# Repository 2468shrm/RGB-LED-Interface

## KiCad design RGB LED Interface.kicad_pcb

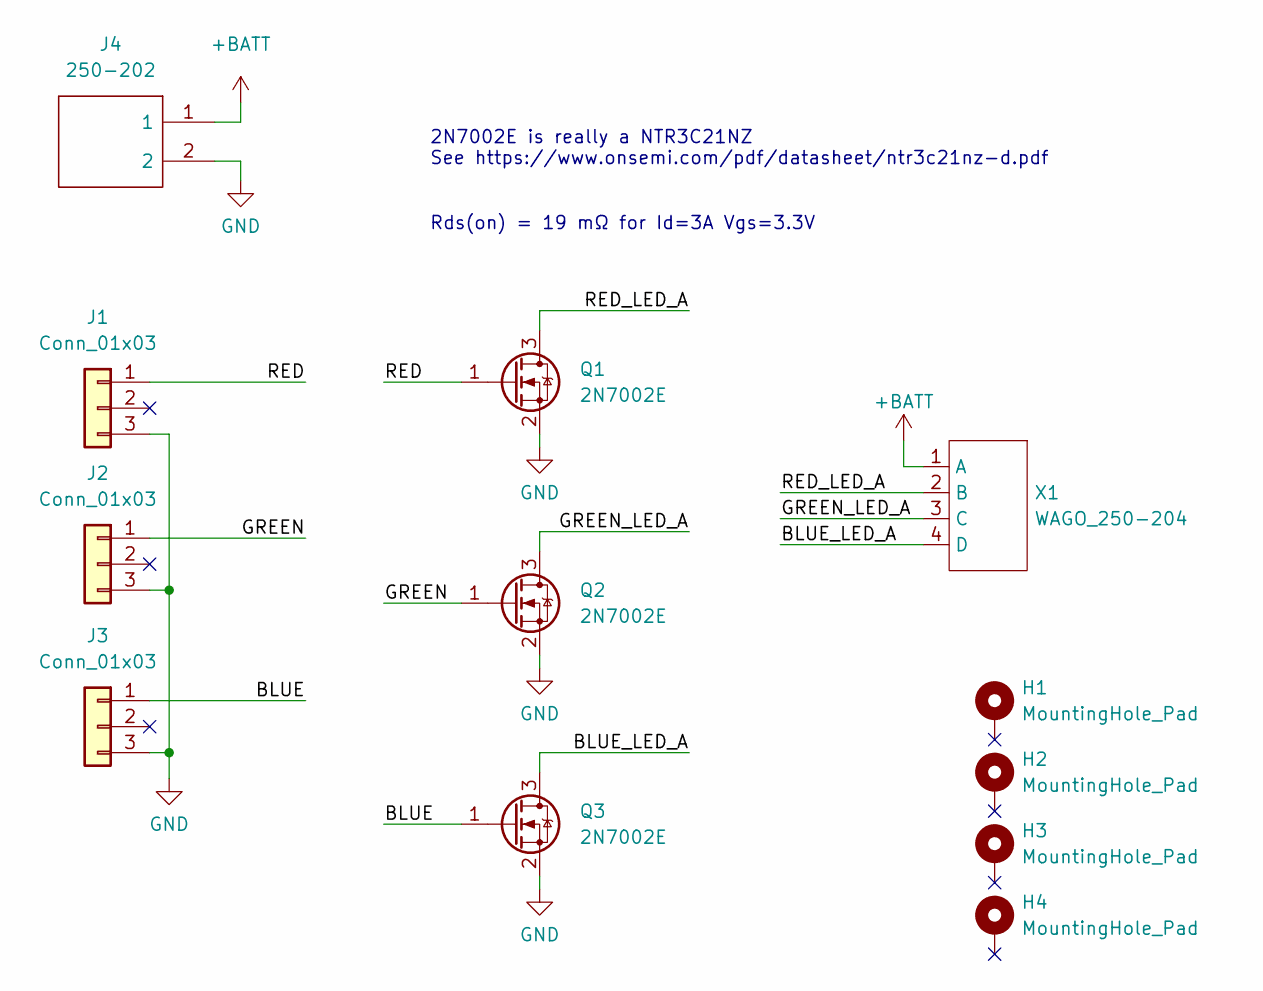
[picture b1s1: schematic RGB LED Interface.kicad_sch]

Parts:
H1: MountingHole_Pad
H2, H3, H4: MountingHole_Pad; MountingHole_2.2mm_M2_ISO7380_Pad
J1, J2, J3: Conn_01x03; PinHeader_1x03_P2.54mm_Vertical
J4: 250-202; 250202; Manufacturer_Part_Number 250-202
Q1, Q2, Q3: 2N7002E; SOT-23
X1: WAGO_250-204; WAGO 250-204

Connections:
+BATT: J4.1, X1.1 (A)
/BLUE: J3.1, Q3.1 (G)
/BLUE_LED_A: Q3.3 (D), X1.4 (D)
/GREEN: J2.1, Q2.1 (G)
/GREEN_LED_A: Q2.3 (D), X1.3 (C)
/RED: J1.1, Q1.1 (G)
/RED_LED_A: Q1.3 (D), X1.2 (B)
GND: J1.3, J2.3, J3.3, J4.2, Q1.2 (S), Q2.2 (S), Q3.2 (S)

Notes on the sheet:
2N7002E is really a NTR3C21NZ See https://www.onsemi.com/pdf/datasheet/ntr3c21nz-d.pdf
Rds(on) = 19 mΩ for Id=3A Vgs=3.3V

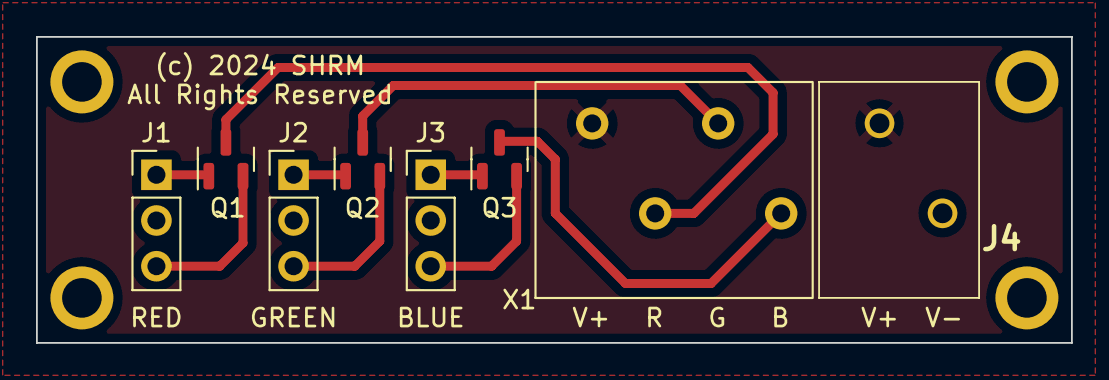
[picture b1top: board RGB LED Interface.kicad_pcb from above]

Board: 2 copper layers, 57.5 x 17.0 mm, 12 parts (0 on the bottom side), 8 nets.

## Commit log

2024-02-24 PCB files

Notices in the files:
RGB LED Interface.kicad_pcb:
(c) 2024 SHRM
All Rights Reserved
